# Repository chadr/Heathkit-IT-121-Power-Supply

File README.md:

# Heathkit IT-121 Power Supply

## Introduction
This is a rechargeable power supply/battery simulator for the Heathkit IT-121 Transistor/FET tester. The goal is to replace the D cells with a rechargeable commodity solution. In this case, 18650 cells.

<picture>
  
</picture>

## Special Thanks to PCBWay!
Thanks to PCBWay for sponsoring this project! The folks at PCBWay are great friends to the maker community. Niche projects like this would not be possible without their support!

Whether for small projects or complex designs, PCBWay offers quality PCB manufacturing, PCBA services, and CNC machining with the industry’s widest and most flexible customization options, all at competitive prices and with high-quality, end-to-end one-stop service. Prototype orders start at a minimum of 5 pieces, with prices as low as $5. Learn more at www.pcbway.com

<picture>

</picture>

## Why Did You Make This?
The IT-121 has some fatal flaws.
1. It uses battery 1, or battery 2, or both batteries in series depending on the test function. Which means the batteries discharge at different rates.
2. Device calibration relies on the batteries to be at equal states of charge.
3. As the batteries drift away from each other, it reaches a point where you cannot maintain calibration (the manual suggest you "split the difference").
4. This means you must frequently replace the D cells.
5. There is no battery door and you must disassemble the device every time.

## Goals and Requirements
* Replace the D cells with long life rechargeable commodity batteries.
* Add ability to charge with commodity wall wart.
* Each D-cell simulator must be able to source 1A, with overhead to handle inrush.
* Each D-cell simulator must maintain 1.5V to prevent the need to constantly re-calibrate device.
* Because current might be drawn from one battery or another, or both in series, there must be positive and negative regulation with a virtual ground at 0V.
* D-cell simulators must provide power with low ripple like the original batteries would.

## Bill of Materials (BoM)
|  **COMPONENT** | **PART**                     |
|:--------------:|------------------------------|
| BT1, BT2       | Keyston 1043                 |
| J1             | 2 Position Screw Terminal    |
| J2, J3         | Molex 6-pin PCIe Right Angle |
| D1             | 1N4001                       |
| R1             | 5.6K 1% 0603                 |
| R2             | 1200R 1% 0603                |
| R3             | 220R 1% 0603                 |
| R5, R6         | 30.1K 1% 0603                |
| IC1            | LT3081ER                     |
| IC2            | LT3091HR                     |
| IC3            | MCP73213T-B6SI/MF            |
| C1, C2, C3, C4 | 100uF 10V SMD Electrolytic   |
| C5, C6, C7, C8 | 1uF 6.3V 0603 Ceramic        |

## Misc Assembly Notes
The power status LED is required for proper regulation. It draws the minimum load current for both regulators.

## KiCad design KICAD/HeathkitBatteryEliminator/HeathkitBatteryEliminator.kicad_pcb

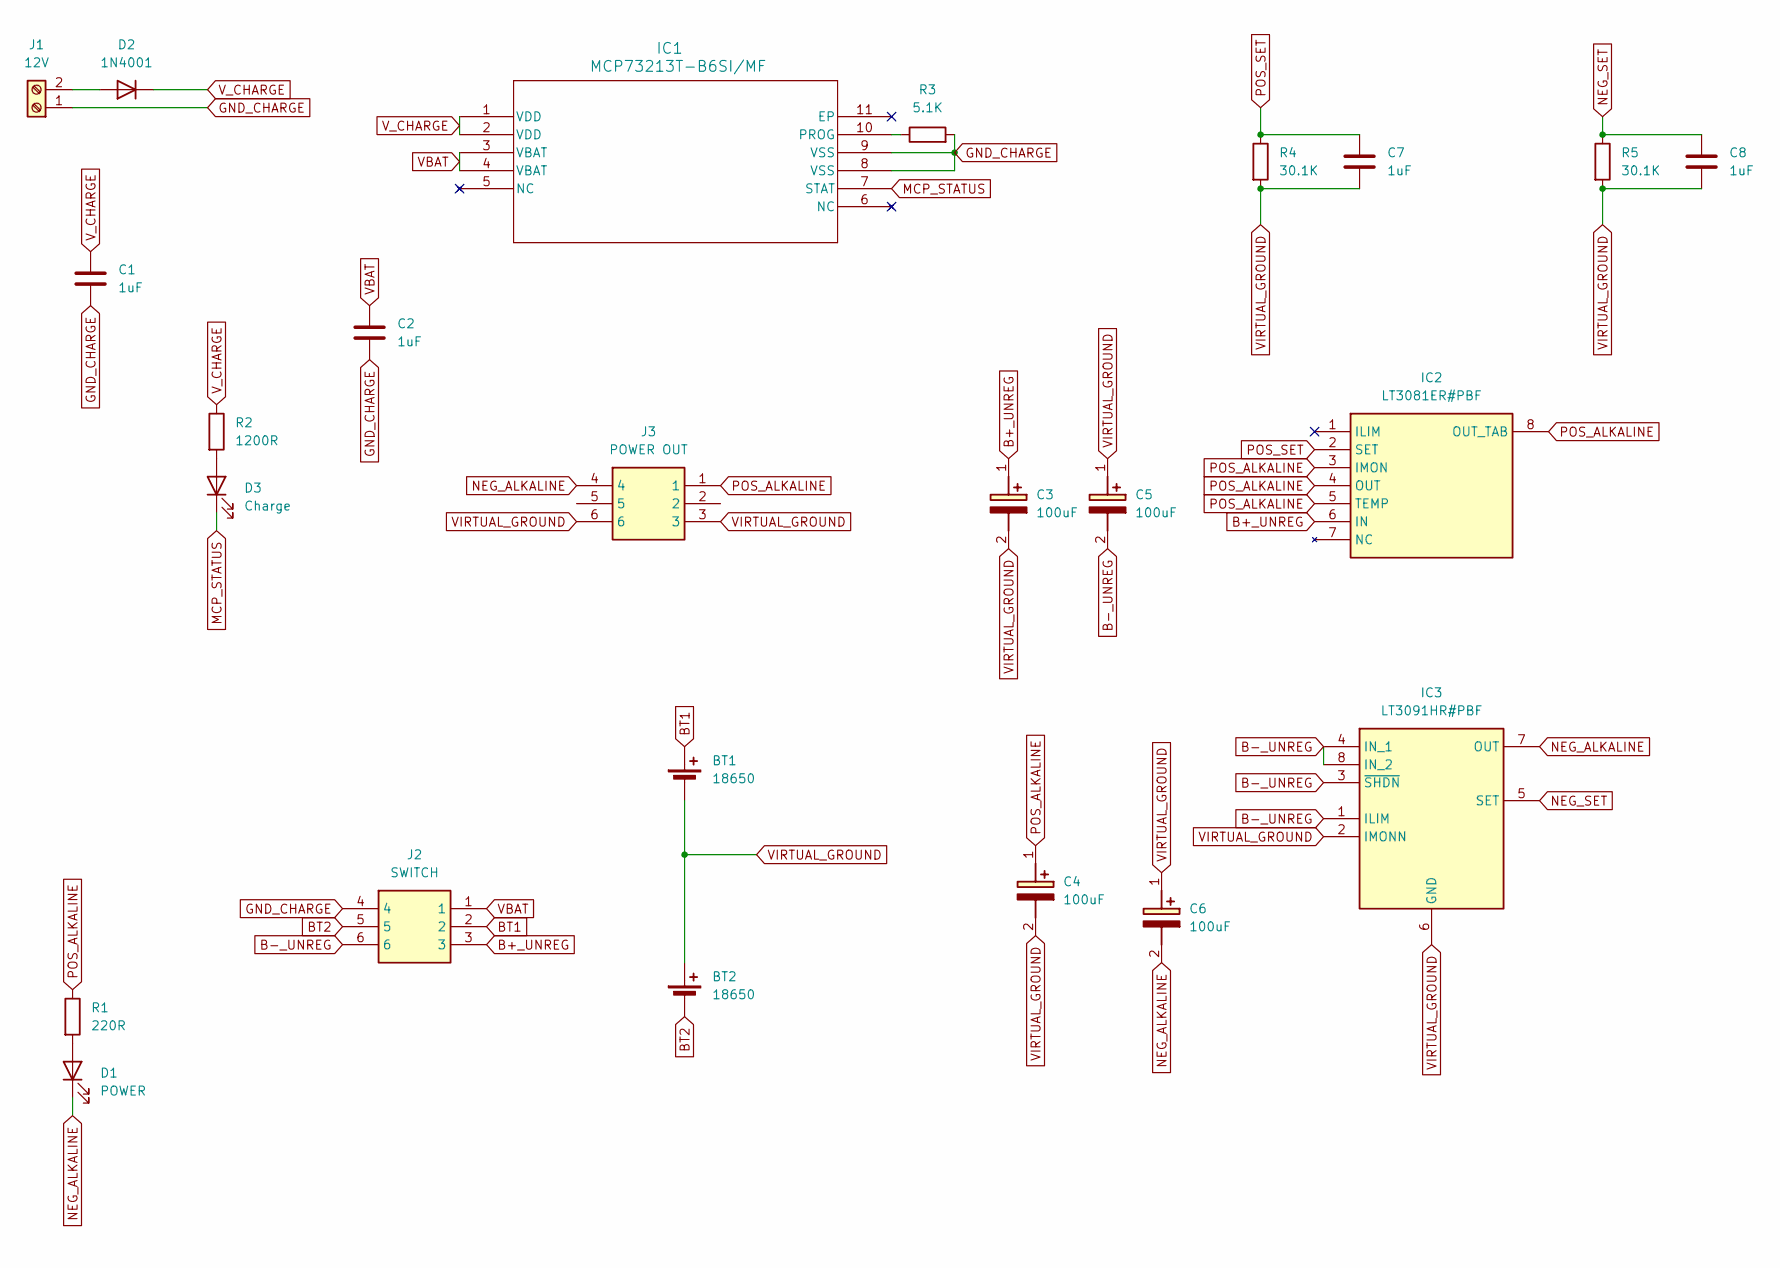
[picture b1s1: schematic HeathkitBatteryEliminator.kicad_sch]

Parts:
BT1, BT2: 18650; 1043
C1, C2: 1uF; C_0603_1608Metric_Pad1.08x0.95mm_HandSolder
C3, C4, C5, C6: 100uF; 865080343009; Manufacturer_Part_Number 865080343009; Mouser Part Number 710-865080343009
C7, C8: 1uF; C_0603_1608Metric
D1: POWER; PinHeader_2x01_P2.54mm_Vertical
D2: 1N4001; D_DO-41_SOD81_P10.16mm_Horizontal
D3: Charge; PinHeader_2x01_P2.54mm_Vertical
IC1: MCP73213T-B6SI/MF; DFN10_3x3MC_MCH-M
IC2: LT3081ER#PBF; TO127P1394X457-8N; Manufacturer_Part_Number LT3081ER#PBF; Mouser Part Number 584-LT3081ER#PBF
IC3: LT3091HR#PBF; LT3091HRPBF; Manufacturer_Part_Number LT3091HR#PBF; Mouser Part Number 584-LT3091HR#PBF
J1: 12V; TerminalBlock_Phoenix_MKDS-1,5-2-5.08_1x02_P5.08mm_Horizont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
J2: SWITCH; 455580003; Manufacturer_Part_Number 45558-0003; Mouser Part Number 538-45558-0003
J3: POWER OUT; 455580003; Manufacturer_Part_Number 45558-0003; Mouser Part Number 538-45558-0003
R1: 220R; R_0603_1608Metric
R2: 1200R; R_0603_1608Metric
R3: 5.1K; R_0603_1608Metric
R4, R5: 30.1K; R_0603_1608Metric

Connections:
B+_UNREG: C3.1 (+), IC2.6 (IN), J2.3
B-_UNREG: C5.2 (-), IC3.1 (ILIM), IC3.3 (~SHDN), IC3.4 (IN_1), IC3.8 (IN_2), J2.6
BT1: BT1.1 (+), J2.2
BT2: BT2.2 (-), J2.5
GND_CHARGE: C1.2, C2.2, IC1.8 (VSS), IC1.9 (VSS), J1.1, J2.4, R3.2
MCP_STATUS: D3.1 (K), IC1.7 (STAT)
NEG_ALKALINE: C6.2 (-), D1.1 (K), IC3.7 (OUT), J3.4
NEG_SET: C8.1, IC3.5 (SET), R5.1
unnamed: D1.2 (A), R1.2
unnamed: D2.2 (A), J1.2
unnamed: D3.2 (A), R2.2
unnamed: IC1.10 (PROG), R3.1
POS_ALKALINE: C4.1 (+), IC2.3 (IMON), IC2.4 (OUT), IC2.5 (TEMP), IC2.8 (OUT_TAB), J3.1, R1.1
POS_SET: C7.1, IC2.2 (SET), R4.1
VBAT: C2.1, IC1.3 (VBAT), IC1.4 (VBAT), J2.1
VIRTUAL_GROUND: BT1.2 (-), BT2.1 (+), C3.2 (-), C4.2 (-), C5.1 (+), C6.1 (+), C7.2, C8.2, IC3.2 (IMONN), IC3.6 (GND), J3.3, J3.6, R4.2, R5.2
V_CHARGE: C1.1, D2.1 (K), IC1.1 (VDD), IC1.2 (VDD), R2.1

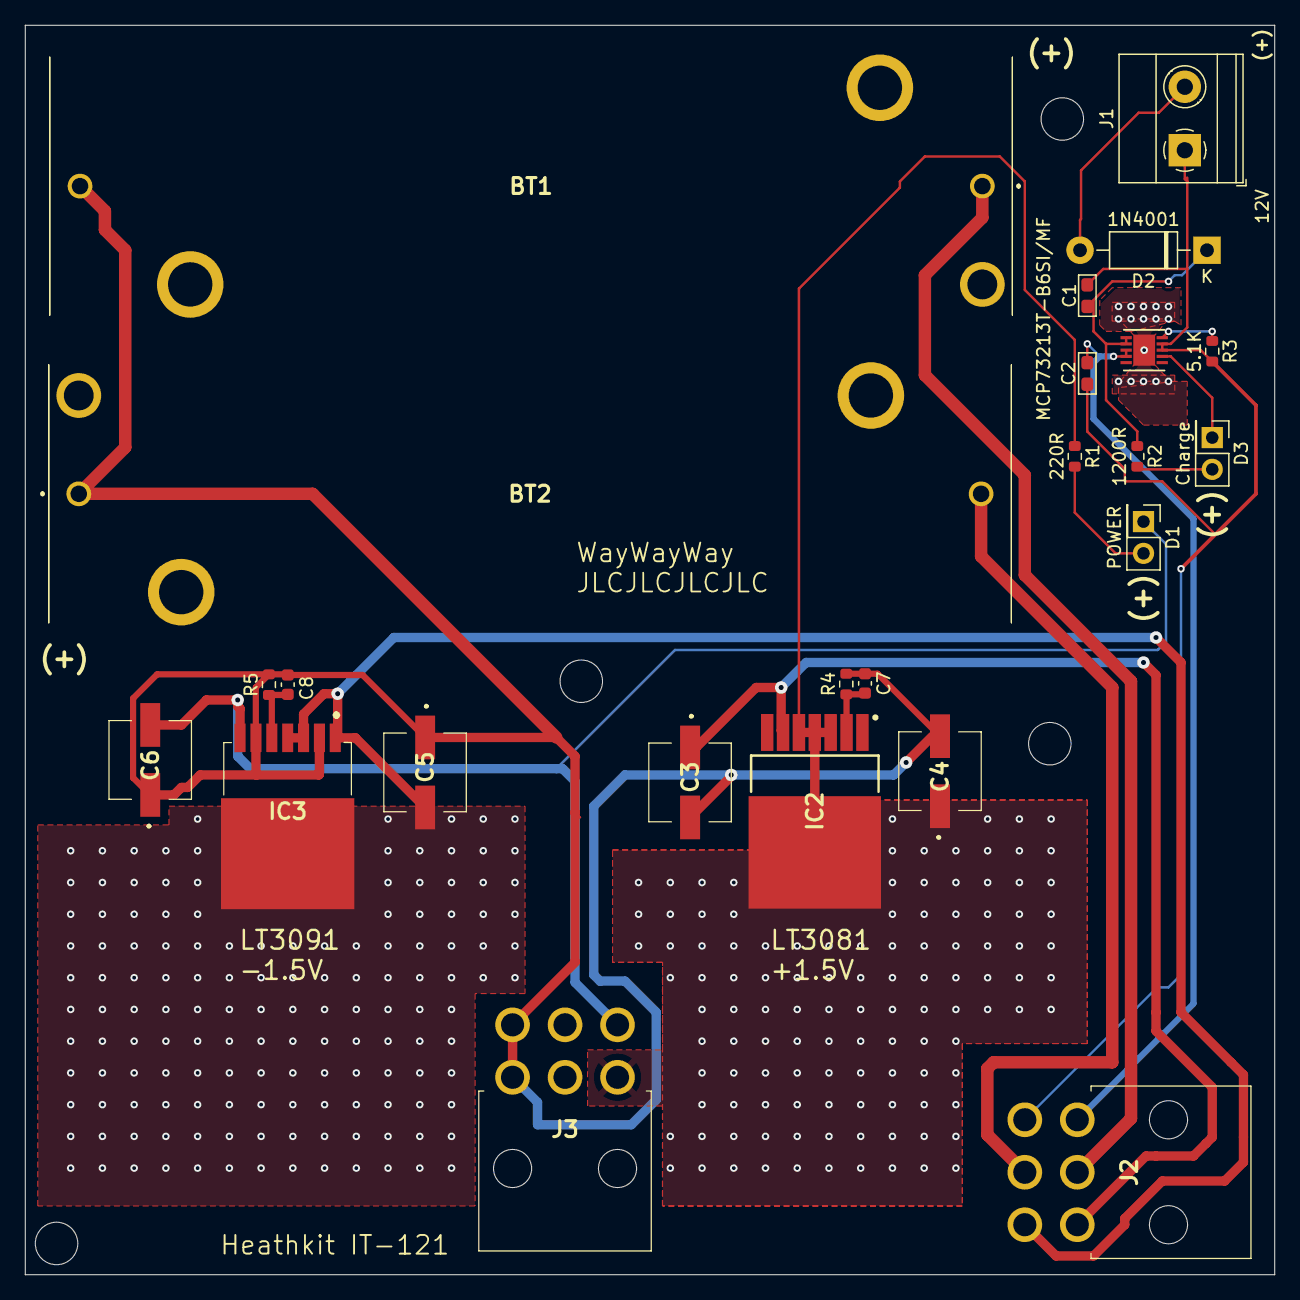
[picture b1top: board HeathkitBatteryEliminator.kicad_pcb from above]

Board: 2 copper layers, 100.0 x 100.0 mm, 24 parts (0 on the bottom side), 17 nets.

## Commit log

2025-07-02 Create ASSEMBLED.jpg
    add images
